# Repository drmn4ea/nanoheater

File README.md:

# nanoheater
Stick-on heater PCB circuit for tiny (2.5 gallon or less) aquaria

This is a hardware design for a novel aquarium heater that adheres to the outside of the tank, avoiding direct contact with water, and is powered by a USB phone charger. More details and pretty pictures are shown at
http://tim.cexx.org/?p=1553

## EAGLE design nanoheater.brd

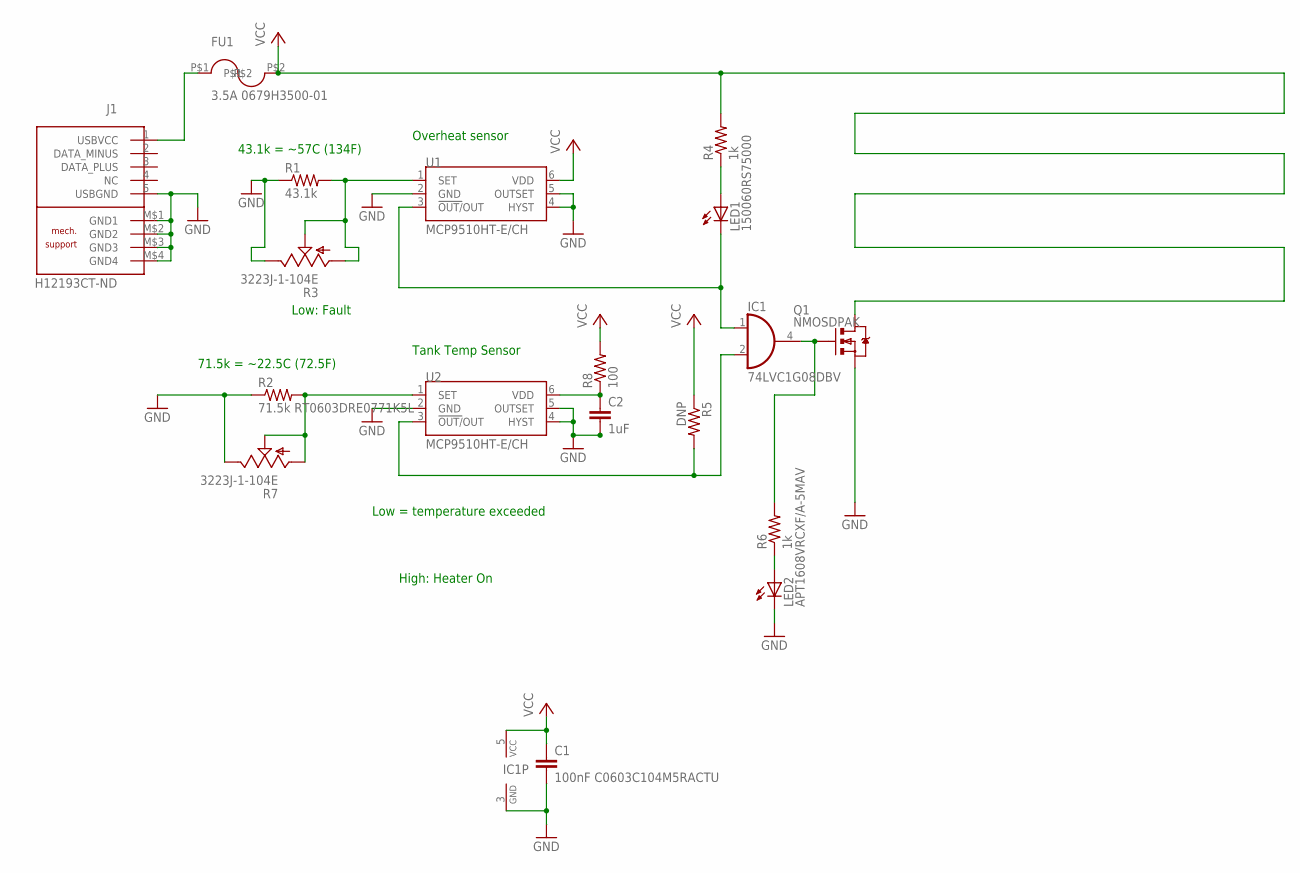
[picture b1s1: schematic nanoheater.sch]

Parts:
C1: 100nF C0603C104M5RACTU; C0603
C2: 1uF; C0603
FU1: 3.5A 0679H3500-01; 2410
IC1: 74LVC1G08DBV; SOT23-5
J1: H12193CT-ND; ZX62WD1-B-5PC_MICRO_USB
LED1: 150060RS75000; CHIP-LED0603
LED2: APT1608VRCXF/A-5MAV; CHIP-LED0603
Q1: NMOSDPAK; DPAK
R1: 43.1k; R0603
R2: 71.5k RT0603DRE0771K5L; R0603
R3, R7: 3223J-1-104E; 3223J
R4, R6: 1k; R0603
R5: DNP; R0603
R8: 100; R0603
U1, U2: MCP9510HT-E/CH; SOT23-6

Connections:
GND: C1.2, C2.2, IC1.3 (GND), J1.5 (USBGND), J1.M$1 (GND1), J1.M$2 (GND2), J1.M$3 (GND3), J1.M$4 (GND4), LED2.C, Q1.3 (S), R1.1, R2.1, R3.3 (E), R7.3 (E), U1.2 (GND), U1.4 (HYST), U1.5 (OUTSET), U2.2 (GND), U2.4 (HYST), U2.5 (OUTSET)
unnamed: IC1.1 (I0), LED1.C, U1.3 (!OUT/!OUT)
unnamed: IC1.2 (I1), R5.2, U2.3 (!OUT/!OUT)
unnamed: FU1.P$1, J1.1 (USBVCC)
unnamed: IC1.4 (O), Q1.1 (G), R6.2
unnamed: LED1.A, R4.1
unnamed: R1.2, R3.1 (A), R3.2 (S), U1.1 (SET)
unnamed: LED2.A, R6.1
unnamed: R2.2, R7.1 (A), R7.2 (S), U2.1 (SET)
unnamed: C2.1, R8.1, U2.6 (VDD)
VCC: C1.1, FU1.P$2, IC1.5 (VCC), Q1.2 (D), R4.2, R5.1, R8.2, U1.6 (VDD)

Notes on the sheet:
Low = temperature exceeded
Low: Fault
High: Heater On
Overheat sensor
Tank Temp Sensor
43.1k = ~57C (134F)
71.5k = ~22.5C (72.5F)

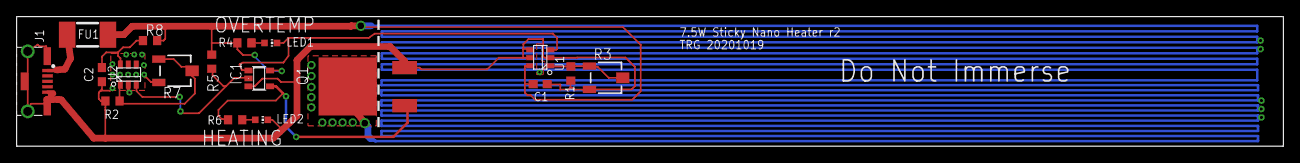
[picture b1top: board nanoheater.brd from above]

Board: 2 copper layers, 152.4 x 15.6 mm, 18 parts (0 on the bottom side), 11 nets.

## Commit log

2021-05-11 First public addition
2021-05-11 Add README.md
